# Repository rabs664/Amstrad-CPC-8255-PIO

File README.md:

# Amstrad CPC 8255 PIO
Simple 8255 PIO board compatible with the Amstrad CPC and MX4 connector.

## Objective
Prototyping board to Learn about the 8255 PIO, and how to write Z80 assembly using an Amstrad CPC.

## Background
Part of a number of modular cards using Z80 associated peripherals and the Amstrad CPC.

## Backplane
[CPC Amstrad Expansion Backplane by revaldinho](https://github.com/revaldinho/cpc_ram_expansion/wiki/CPC-Expansion-Backplane)

## IO Addressing
The IO Address can be selected using two sets of jumpers (CS_HB and CS_LB), supporting the following base address.

* F8E0 and F8F0
* F9E0 and F9F0
* FAE0 and FAF0
* FBE0 and FBF0

See [CPC Wiki IO Port Summary](https://www.cpcwiki.eu/index.php/I/O_Port_Summary) for a list of known IO ports used on the Amstrad CPC.

## Testing
The 8255 PIO board has been built and has been tested on an Amstrad CPC 6128.

## PCBs
PCBs are available from [Seeed Studio V2.0](https://www.seeedstudio.com/Amstrad-CPC-8255-PIO-g-1393845) or [Seeed Studio V3.1](https://www.seeedstudio.com/Simple-8255-PIO-board-compatible-with-the-Amstrad-CPC-and-MX4-connector-V3--g-1396645)

## Components
This [Digi-Key List](https://www.digikey.co.uk/en/mylists/list/ZWWIHRPLO7 ) contains all components excluding the 8255 which was purchased from EBay.

Note the right angled header for the port connections was not available at the time of producing this list but all other components were in stock for shipping immediately.

## Assembler
[RASM](https://github.com/EdouardBERGE/rasm)

## Resources
[CPCWiki](https://www.cpcwiki.eu/index.php/Main_Page)

Z80 Application by James W Coffron ISBN 0-89588-094-6

## Acknowledgements
[@revaldinho](https://github.com/revaldinho)

Don Prefontaine 

Peter Murray

[@EdouardBERGE](https://github.com/EdouardBERGE)

# Release History
## Version 2.0
* First Release
## Version 3.1
* KiCad created version of PCB.

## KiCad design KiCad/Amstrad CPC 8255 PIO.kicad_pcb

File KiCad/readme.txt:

This folder contains files associated with the use of KiCad to create the schematics and PCB.

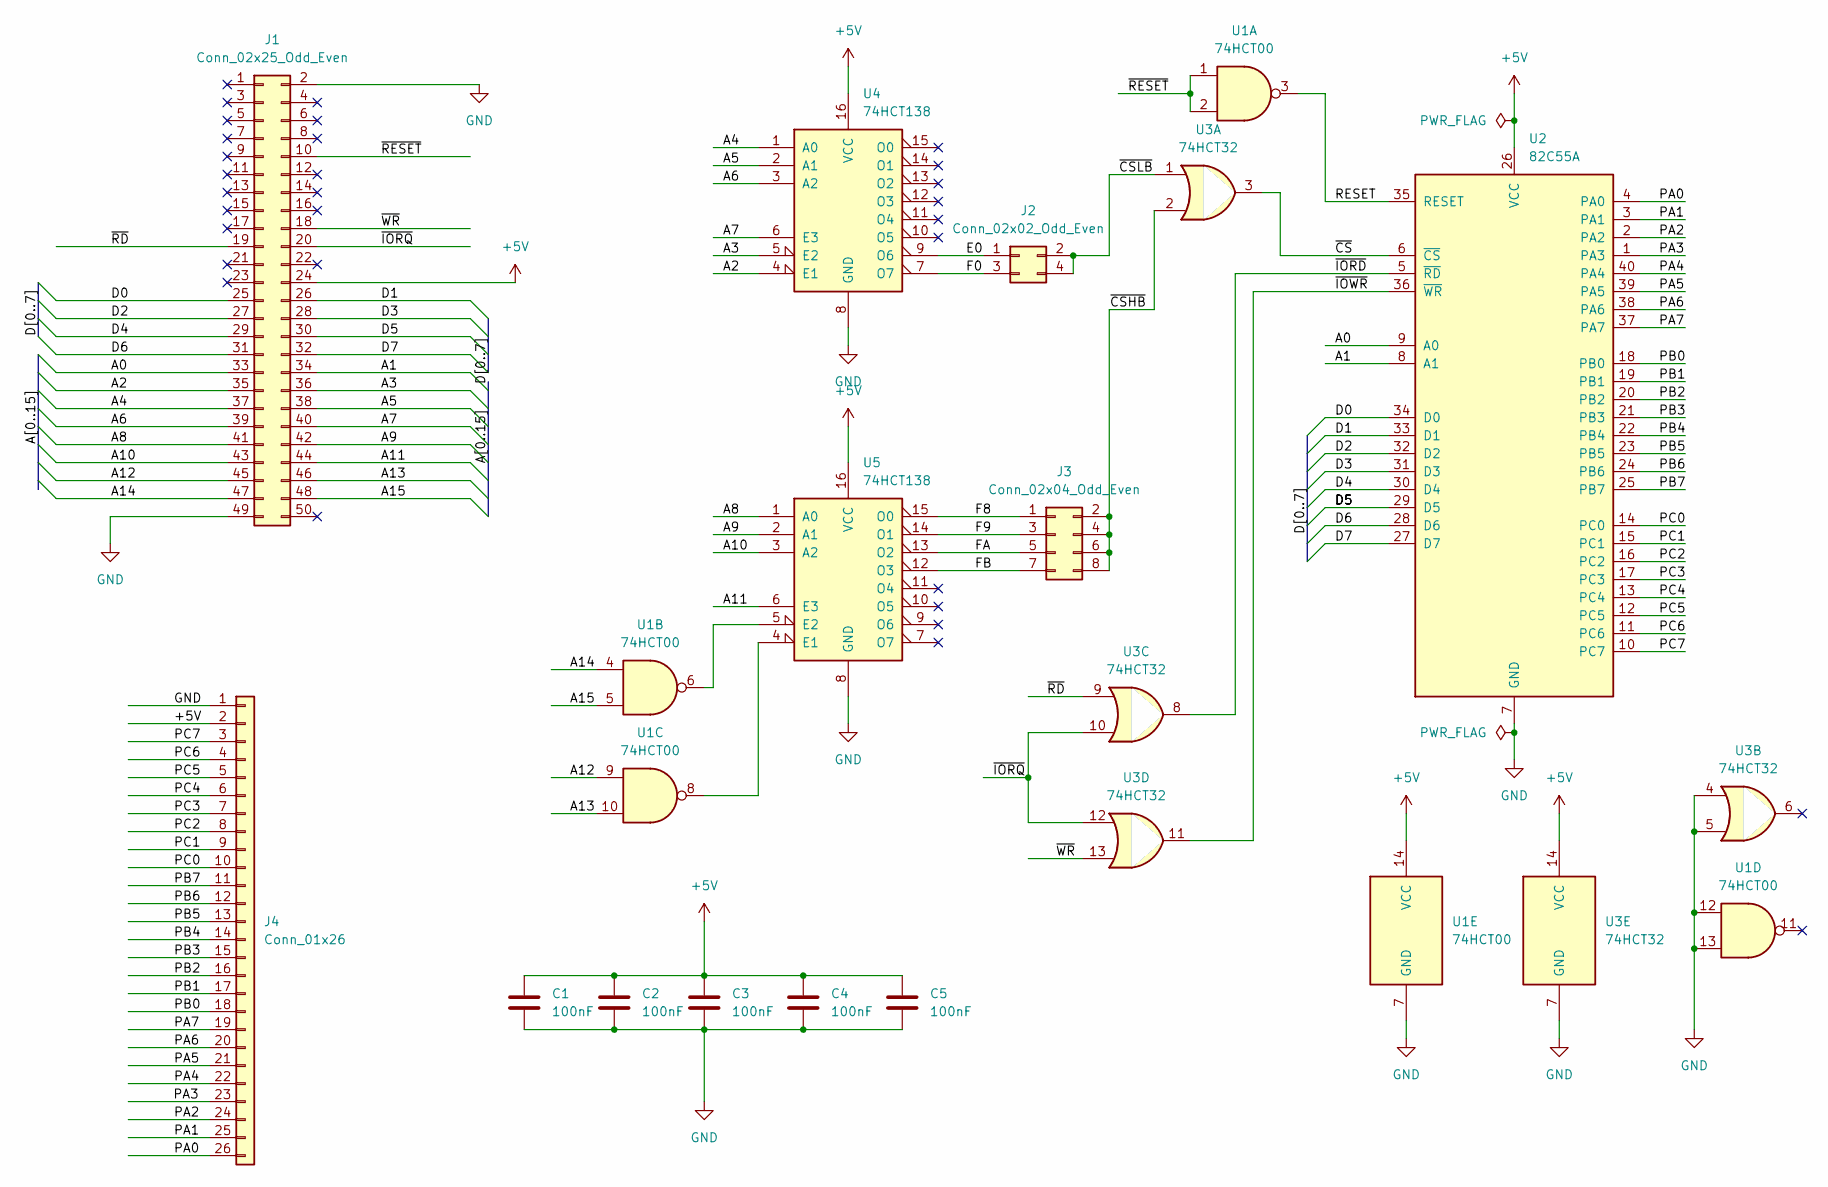
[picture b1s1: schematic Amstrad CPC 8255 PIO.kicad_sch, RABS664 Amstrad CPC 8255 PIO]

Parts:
C1, C2, C3, C4, C5: 100nF; C_Disc_D5.0mm_W2.5mm_P5.00mm; DigiKey 56-K104K15X7RF53H5G-ND
J1: Conn_02x25_Odd_Even; IDC-Header_2x25_P2.54mm_Horizontal; DigiKey 3M157291-ND
J2: Conn_02x02_Odd_Even; PinHeader_2x02_P2.54mm_Vertical
J3: Conn_02x04_Odd_Even; PinHeader_2x04_P2.54mm_Vertical
J4: Conn_01x26; PinHeader_1x26_P2.54mm_Horizontal
U1: 74HCT00; DIP-14_W7.62mm_Socket_LongPads; DigiKey 296-2081-5-ND
U2: 82C55A; DIP-40_W15.24mm_Socket_LongPads
U3: 74HCT32; DIP-14_W7.62mm_Socket_LongPads; Digikey 296-2112-5-ND
U4, U5: 74HCT138; DIP-16_W7.62mm_Socket_LongPads; DigiKey 296-2091-5-ND

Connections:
+5V: C1.1, C2.1, C3.1, C4.1, C5.1, J1.24, J4.2, U1.14 (VCC), U2.26 (VCC), U3.14 (VCC), U4.16 (VCC), U5.16 (VCC)
/A0: J1.33, U2.9 (A0)
/A1: J1.34, U2.8 (A1)
/A2: J1.35, U4.4 (E1)
/A3: J1.36, U4.5 (E2)
/A4: J1.37, U4.1 (A0)
/A5: J1.38, U4.2 (A1)
/A6: J1.39, U4.3 (A2)
/A7: J1.40, U4.6 (E3)
/A8: J1.41, U5.1 (A0)
/A9: J1.42, U5.2 (A1)
/A10: J1.43, U5.3 (A2)
/A11: J1.44, U5.6 (E3)
/A12: J1.45, U1.9
/A13: J1.46, U1.10
/A14: J1.47, U1.4
/A15: J1.48, U1.5
/D0: J1.25, U2.34 (D0)
/D1: J1.26, U2.33 (D1)
/D2: J1.27, U2.32 (D2)
/D3: J1.28, U2.31 (D3)
/D4: J1.29, U2.30 (D4)
/D5: J1.30, U2.29 (D5)
/D6: J1.31, U2.28 (D6)
/D7: J1.32, U2.27 (D7)
/E0: J2.1, U4.9 (O6)
/F0: J2.3, U4.7 (O7)
/F8: J3.1, U5.15 (O0)
/F9: J3.3, U5.14 (O1)
/FA: J3.5, U5.13 (O2)
/FB: J3.7, U5.12 (O3)
/PA0: J4.26, U2.4 (PA0)
/PA1: J4.25, U2.3 (PA1)
/PA2: J4.24, U2.2 (PA2)
/PA3: J4.23, U2.1 (PA3)
/PA4: J4.22, U2.40 (PA4)
/PA5: J4.21, U2.39 (PA5)
/PA6: J4.20, U2.38 (PA6)
/PA7: J4.19, U2.37 (PA7)
/PB0: J4.18, U2.18 (PB0)
/PB1: J4.17, U2.19 (PB1)
/PB2: J4.16, U2.20 (PB2)
/PB3: J4.15, U2.21 (PB3)
/PB4: J4.14, U2.22 (PB4)
/PB5: J4.13, U2.23 (PB5)
/PB6: J4.12, U2.24 (PB6)
/PB7: J4.11, U2.25 (PB7)
/PC0: J4.10, U2.14 (PC0)
/PC1: J4.9, U2.15 (PC1)
/PC2: J4.8, U2.16 (PC2)
/PC3: J4.7, U2.17 (PC3)
/PC4: J4.6, U2.13 (PC4)
/PC5: J4.5, U2.12 (PC5)
/PC6: J4.4, U2.11 (PC6)
/PC7: J4.3, U2.10 (PC7)
/RESET: U1.3, U2.35 (RESET)
/~CSHB: J3.2, J3.4, J3.6, J3.8, U3.2
/~CSLB: J2.2, J2.4, U3.1
/~CS: U2.6 (~CS), U3.3
/~IORD: U2.5 (~RD), U3.8
/~IORQ: J1.20, U3.10, U3.12
/~IOWR: U2.36 (~WR), U3.11
/~RD: J1.19, U3.9
/~RESET: J1.10, U1.1, U1.2
/~WR: J1.18, U3.13
GND: C1.2, C2.2, C3.2, C4.2, C5.2, J1.2, J1.49, J4.1, U1.7 (GND), U1.12, U1.13, U2.7 (GND), U3.4, U3.5, U3.7 (GND), U4.8 (GND), U5.8 (GND)
unnamed: U1.8, U5.4 (E1)
unnamed: U1.6, U5.5 (E2)

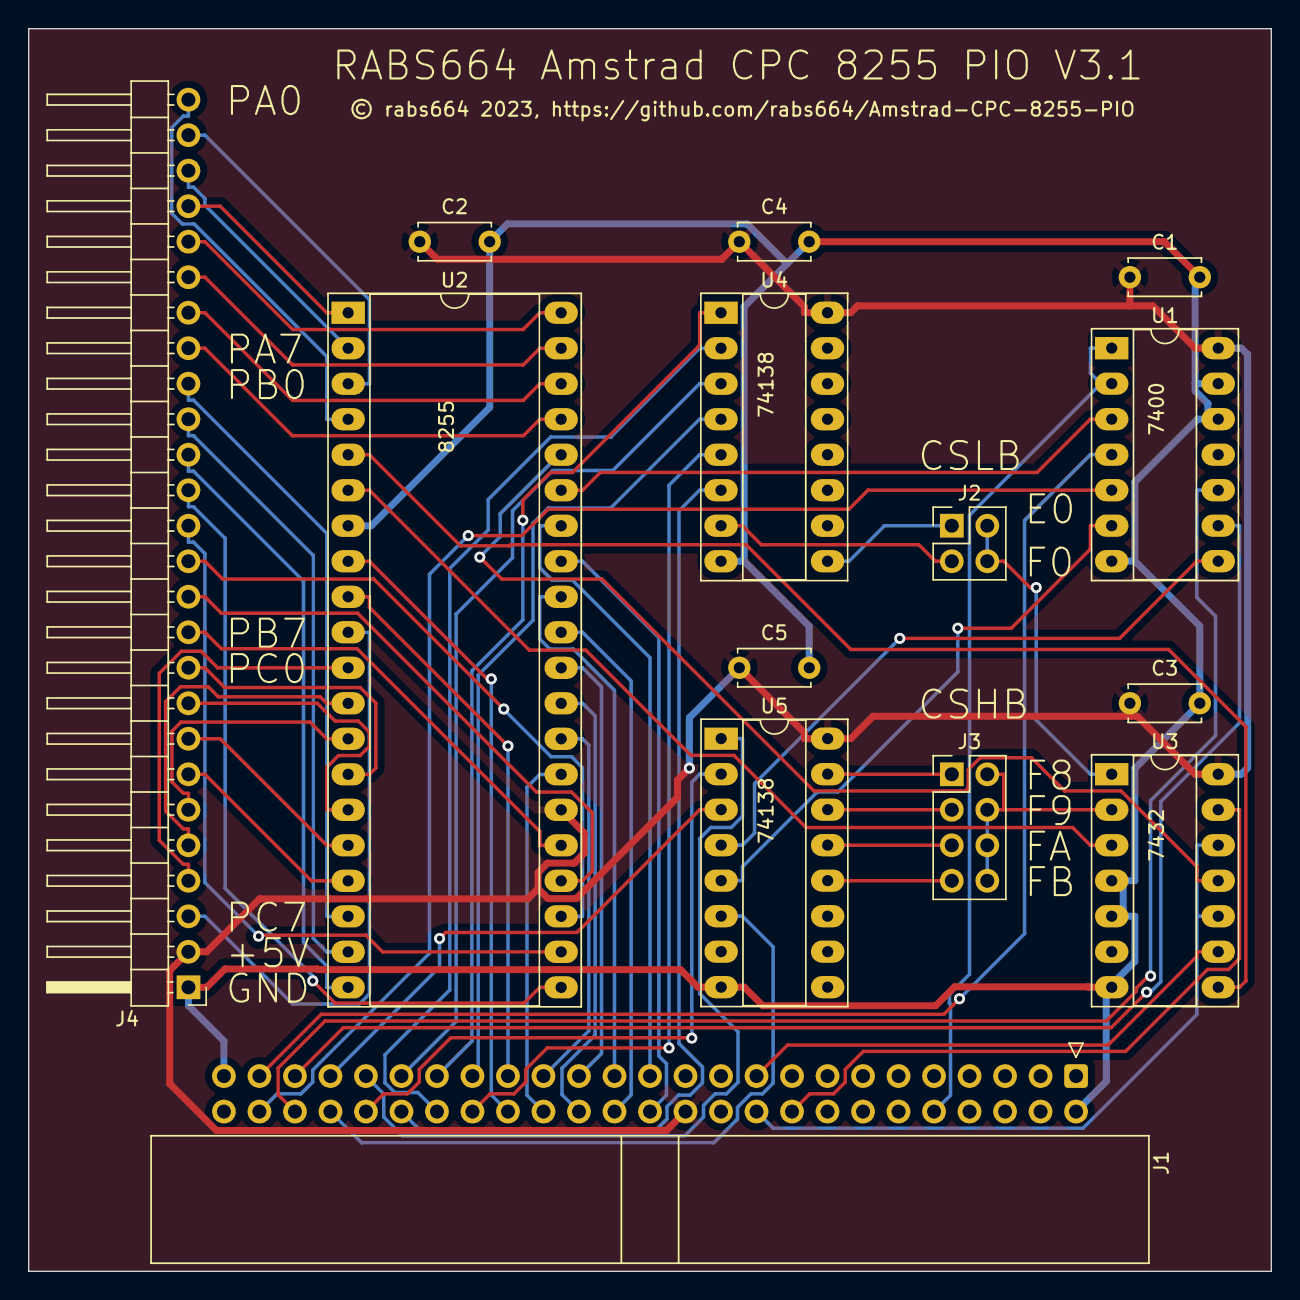
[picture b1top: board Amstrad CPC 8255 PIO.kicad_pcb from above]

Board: 2 copper layers, 88.9 x 88.9 mm, 14 parts (0 on the bottom side), 68 nets.

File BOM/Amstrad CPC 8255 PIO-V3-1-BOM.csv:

"#","Reference","Qty","Value","Footprint","DNP"
"1","C1, C2, C3, C4, C5","5","100nF","Capacitor_THT:C_Disc_D5.0mm_W2.5mm_P5.00mm",""
"2","J1","1","Conn_02x25_Odd_Even","Connector_IDC:IDC-Header_2x25_P2.54mm_Horizontal",""
"3","J2","1","Conn_02x02_Odd_Even","Connector_PinHeader_2.54mm:PinHeader_2x02_P2.54mm_Vertical",""
"4","J3","1","Conn_02x04_Odd_Even","Connector_PinHeader_2.54mm:PinHeader_2x04_P2.54mm_Vertical",""
"5","J4","1","Conn_01x26","Connector_PinHeader_2.54mm:PinHeader_1x26_P2.54mm_Horizontal",""
"6","U1","1","74HCT00","Package_DIP:DIP-14_W7.62mm_Socket_LongPads",""
"7","U2","1","82C55A","Package_DIP:DIP-40_W15.24mm_Socket_LongPads",""
"8","U3","1","74HCT32","Package_DIP:DIP-14_W7.62mm_Socket_LongPads",""
"9","U4, U5","2","74HCT138","Package_DIP:DIP-16_W7.62mm_Socket_LongPads",""

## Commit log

2023-05-28 Update README.md
    First update
2023-05-28 Create readme.txt
    folder readme description.
2023-05-28 Add files via upload
    First Release, changed name of files from Z80 PIO to 8255 PIO.
2023-05-28 Create Software-Files
2023-06-17 Update README.md
    Typo
2023-06-17 Update readme.txt
    Typo
2023-06-24 Changed to use RASM
2023-08-25 Update README.md
    Updated Seeed Studio References for PCBs
2024-01-26 Uploaded KiCad 7.0 schematic for version 3.1
    Noted that there was not a jpg image for version 3.1 board which was created in KiCad 7.0
2024-01-26 Added BOM from KiCAD 7.0 for version 3.1
    Noted that BOM only existed for version 2.0
2024-01-27 Pictures of Test Breaboard and v3.1
    Some picture of the test breadboard used and when connected to the V3.1 PIO board.
2024-01-27 Correct Logic Family for 74 245 ICs to use HCT.
2024-01-27 Delete Images/Amstrad-CPC-2855-PIO-Test-1-0.png
    Replaced by Amstrad-CPC-8255-PIO-Test-1-1.png with a correct to the logic family using HCT.
2025-07-20 Update README.md
    Removed invalid URL links

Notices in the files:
KiCad/Amstrad CPC 8255 PIO.kicad_pcb:
© rabs664 2023, https://github.com/rabs664/Amstrad-CPC-8255-PIO
